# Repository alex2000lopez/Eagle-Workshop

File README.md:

# Eagle Workshop
FIles for Eagle Workshop 19/08/2019

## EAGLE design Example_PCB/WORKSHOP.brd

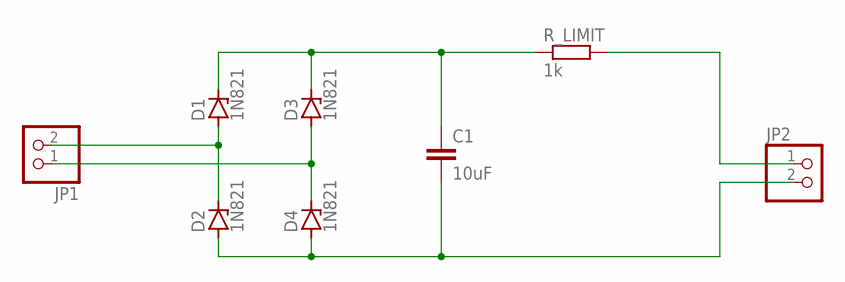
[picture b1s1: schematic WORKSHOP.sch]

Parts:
C1: 10uF; C2.5-6
D1, D2, D3, D4: 1N821; DO35Z10
JP1, JP2: PINHD-1X2; 1X02
R_LIMIT: 1k; 0207/12

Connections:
unnamed: JP2.1, R_LIMIT.2
unnamed: D1.A, D2.C, JP1.2
unnamed: C1.2, D2.A, D4.A, JP2.2
unnamed: C1.1, D1.C, D3.C, R_LIMIT.1
unnamed: D3.A, D4.C, JP1.1

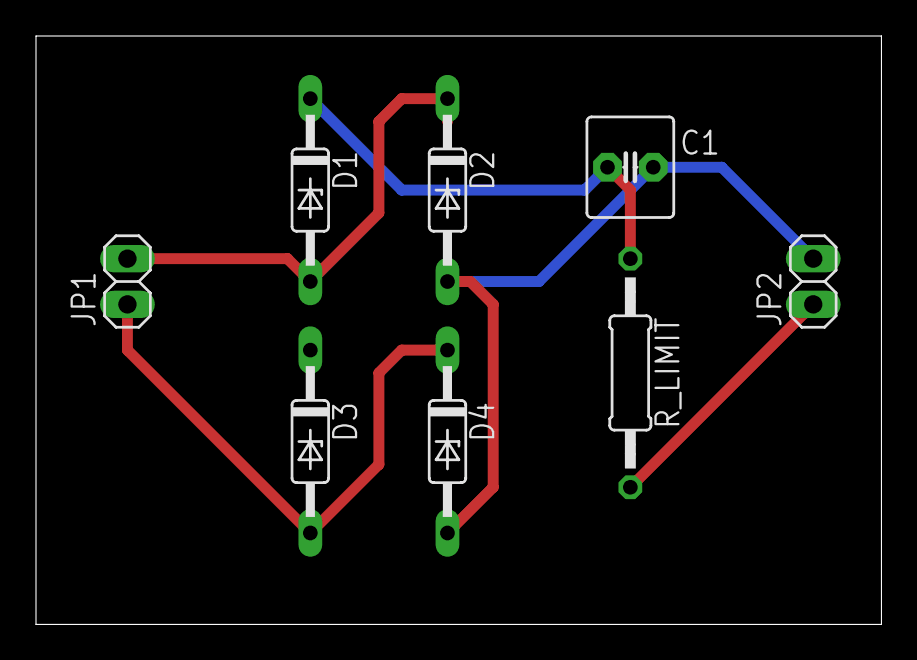
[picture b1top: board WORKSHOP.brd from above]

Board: 2 copper layers, 47.0 x 32.7 mm, 8 parts (0 on the bottom side), 5 nets.
